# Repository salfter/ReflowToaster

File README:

This is a re-creation in KiCad of this project:

https://upverter.com/salfter/129531d44b9b2c59/ReflowToaster2/

which also depends on this project:

https://upverter.com/salfter/f2bd7fd7ccbdb49b/DuinoModSingle/

It's a single-board mashup of the Rocket Scream reflow controller shield and
an Arduino Leonardo:

http://www.rocketscream.com/shop/reflow-oven-controller-shield-arduino-compatible
http://arduino.cc/en/Main/arduinoBoardLeonardo

As such, I anticipate that the Rocket Scream software should run on this
with little or no modification:

https://github.com/rocketscream/Reflow-Oven-Controller

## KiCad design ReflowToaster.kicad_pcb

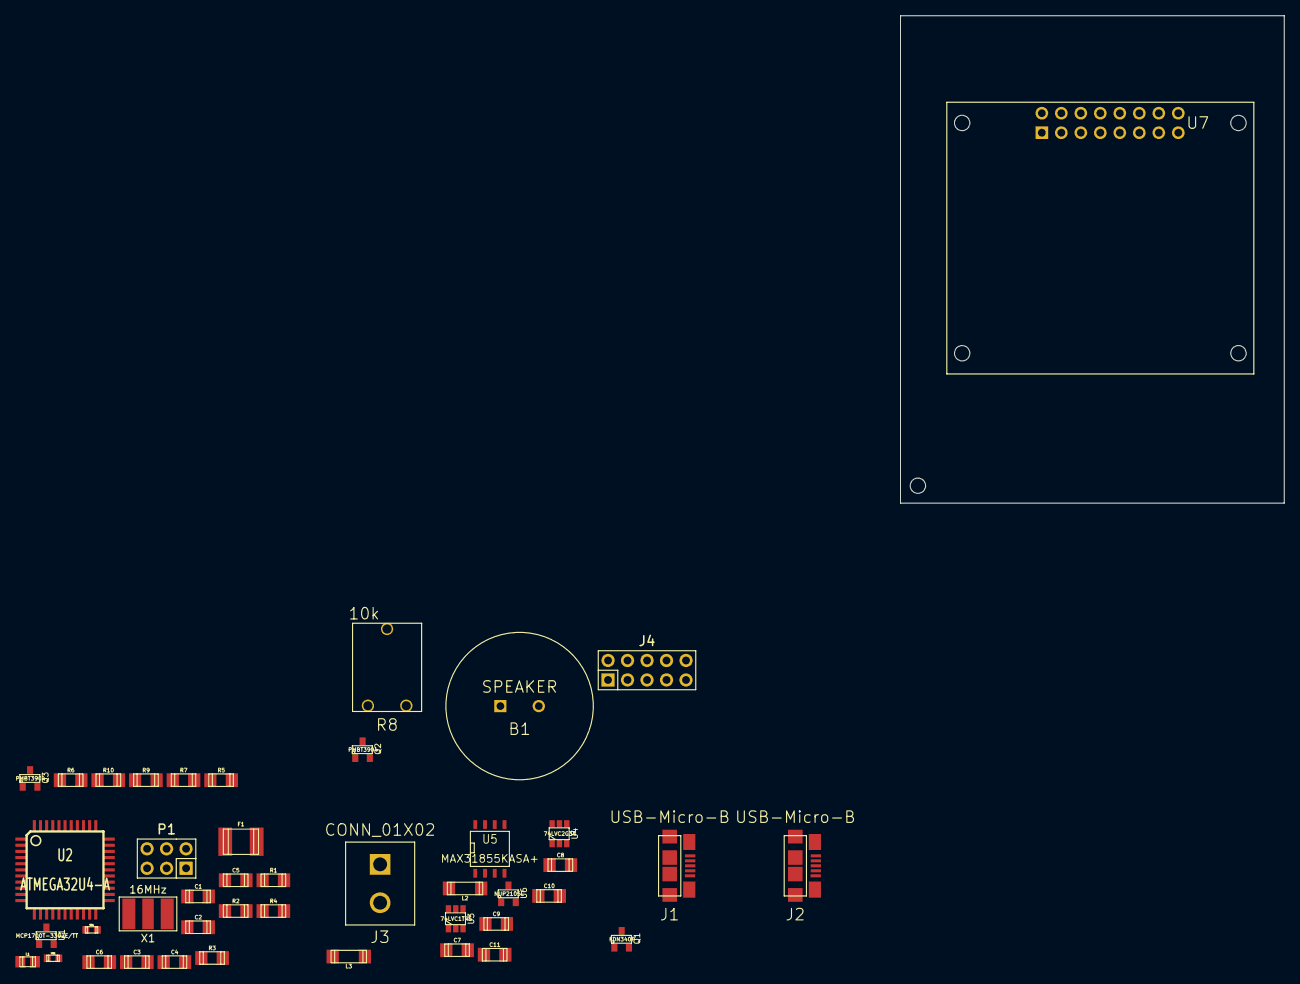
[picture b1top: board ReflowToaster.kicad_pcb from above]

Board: 2 copper layers, 50.0 x 63.5 mm, 45 parts (0 on the bottom side), 47 nets, no tracks yet.

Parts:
B1: SPEAKER; CX-0905C
C1, C2, C3: 1uF; c_1206
C4, C5, C6, C7, C8, C9, C10: 0.1uF; c_1206
C11: 0.01uF; c_1206
F1: 500mA; c_1812
J1, J2: USB-Micro-B; FCI_10118192-0001LF
J3: CONN_01X02; 282836-2
J4: CONN_02X05; Pin_Header_Straight_2x05
L1: Ferrite Bead; c_0805
L2, L3: INDUCTOR_SMALL; smd_1806
MH: MountingHole_2mm
P1: CONN_02X03; Socket_Strip_Straight_2x03
Q1: FDN340P
Q2, Q3: PMBT3904; SOT-23
R1, R2: 22; c_1206
R3, R4, R5, R6, R9: 10k; c_1206
R7: 1k; c_1206
R8: 10k; 3319P-1-103
R10: 47k; c_1206
U1: MCP1700T-3302E/TT; SOT-23
U2: ATMEGA32U4-A; TQFP-44
U3: 74LVC1T45; SOT-23-6
U4: 74LVC2G34; SOT-23-6
U5: MAX31855KASA+; SOIC-8-N
U6: NUP2105L; SOT-23
U7: LCD8X2; LCD_8x2
VR1, VR2: VR; c_0603
X1: 16MHz; AVX_PBRC-H

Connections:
+3.3V: C2.1, C8.1, C9.1, C10.1, U1.2, U3.6, U5.4
+5V: B1.1, C1.1, C5.1, C7.1, F1.2, J4.1, J4.3, L1.1, P1.2, R4.1, R5.1, R8.1, U1.3, U2.2, U2.7, U2.14, U2.34, U2.44, U3.1, U7.2, U7.15
/DuinoModSingle/4/A6: R7.2, U2.25
/DuinoModSingle/5/PWM: R10.2, U2.31
/DuinoModSingle/6/PWM/A8: R9.2, U2.27
/DuinoModSingle/7: U2.1, U7.4
/DuinoModSingle/8/A9: U2.28, U7.6
/DuinoModSingle/9/PWM/A10: U2.29, U7.11
/DuinoModSingle/10/PWM/A11: U2.30, U7.12
/DuinoModSingle/11/PWM: U2.12, U7.13
/DuinoModSingle/12/A7: U2.26, U7.14
/DuinoModSingle/A1: U2.37, U4.1
/DuinoModSingle/A2: U2.38, U4.3
/DuinoModSingle/A3: U2.39, U3.3
/DuinoModSingle/AREF: C4.1, U2.42
/DuinoModSingle/MISO: P1.1, U2.11
/DuinoModSingle/MOSI: P1.4, U2.10
/DuinoModSingle/SCK: P1.3, U2.9
/DuinoModSingle/USB_5V: F1.1, Q1.S
/DuinoModSingle/USB_D+: J2.3, R2.2, VR2.1
/DuinoModSingle/USB_D-: J2.2, R1.2, VR1.1
/DuinoModSingle/~RESET: J4.10, P1.5, R4.2, U2.13
BTN1: J4.6, R5.2, R6.1, U2.36
BTN2: J4.8, R6.2
GND: C1.2, C2.2, C3.2, C4.2, C5.2, C6.2, C7.2, C8.2, C9.2, C10.2, J1.4, J1.5, J1.6, J1.7, J1.8, J1.9, J1.10, J1.11, J2.4, J2.5, J2.6, J2.7, J2.8, J2.9, J2.10, J2.11, J4.5, J4.7, J4.9, P1.6, Q2.2, Q3.2, R3.1, R8.2, U1.1, U2.5, U2.15, U2.23, U2.35, U2.43, U3.2, U3.5, U4.2, U5.1, U6.3, U7.1, U7.5, U7.16, VR1.2, VR2.2, X1.3
LED: J4.2, R7.1
unnamed: B1.2, Q2.3
unnamed: C3.1, U2.6
unnamed: C6.1, L1.2, U2.24
unnamed: C11.1, L2.1, U5.3, U6.2
unnamed: C11.2, L3.1, U5.2, U6.1
unnamed: J1.1, Q1.G
unnamed: J2.1, Q1.D
unnamed: J3.1, L2.2
unnamed: J3.2, L3.2
unnamed: Q2.1, R9.1
unnamed: Q3.1, R10.1
unnamed: R1.1, U2.3
unnamed: R2.1, U2.4
unnamed: R3.2, U2.33
unnamed: R8.3, U7.3
unnamed: U2.16, X1.2
unnamed: U2.17, X1.1
unnamed: U3.4, U5.7
unnamed: U4.4, U5.6
unnamed: U4.6, U5.5
SSR: J4.4, Q3.3

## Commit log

2014-09-09 add project-specififc library
2014-09-09 schematic closer to complete
2014-09-09 add footprint for resonator
2014-09-09 remove duplicate crystal symbol from library
2014-09-09 DuinoModSingle complete
2014-09-09 more changes
2014-09-10 add footprint for USB connectors
2014-09-10 add FDN340P
2014-09-10 add MAX31855
2014-09-10 new sheet
2014-09-10 add README
2014-09-10 add CC BY-SA 4.0 license
2014-09-10 more components added
2014-09-10 working on thermocouple section now
2014-09-10 thermocouple section complete
2014-09-11 schematic complete
2014-09-11 add part info for speaker
2014-09-11 DuinoModSingle & main sheet tagged with vendor part #s for BOM generation
2014-09-11 updated netlist
2014-09-11 remove some extra whitespace
2014-09-12 add BOM generator script
2014-09-12 last of the new footprints added; PCB started
2014-09-12 components tagged with vendor part IDs
2014-09-13 fix incorrect vendor part number
2014-09-13 redo annotation
2014-09-13 more work
2014-09-15 don't need extra-components file anymore
